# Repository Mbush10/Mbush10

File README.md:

- 👋 Hi, I’m @Mbush10
- 👀 I’m interested in ...
- 🌱 I’m currently learning ...
- 💞️ I’m looking to collaborate on ...
- 📫 How to reach me ...

<!---
Mbush10/Mbush10 is a ✨ special ✨ repository because its `README.md` (this file) appears on your GitHub profile.
You can click the Preview link to take a look at your changes.
--->

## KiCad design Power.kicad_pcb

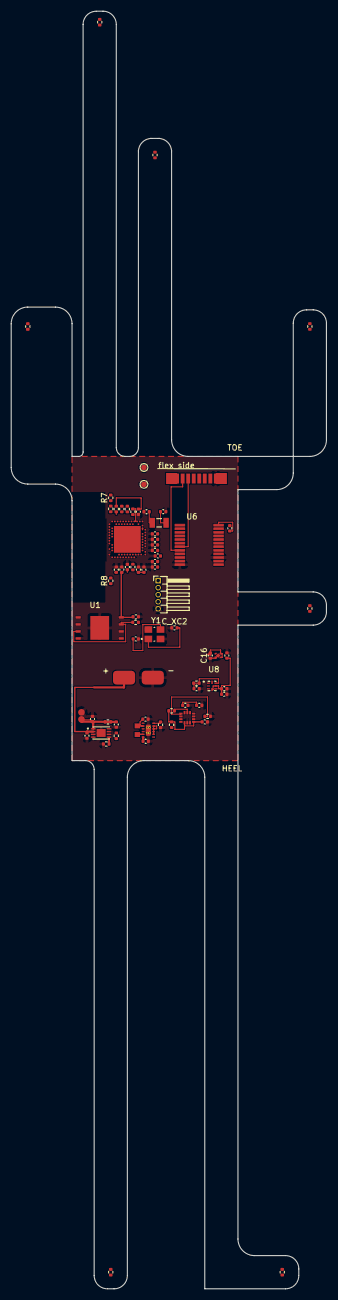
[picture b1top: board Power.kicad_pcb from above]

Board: 2 copper layers, 57.0 x 231.0 mm, 73 parts (0 on the bottom side), 53 nets.

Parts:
C1: 0.1uF; C_0402_1005Metric
C2, C3: 10µF; C_0402_1005Metric
C4, C12, C13, C14, C19, C20, C21: 100nF; C_0402_1005Metric
C5, C6, C7, C8, C9, C10, C11: C; C_0402_1005Metric
C15: 1 µF; C_0402_1005Metric
C16, C17: 1µF; C_0402_1005Metric
C18: 4.7nF; C_0402_1005Metric
C_IMU_IO1: 100nF; C_0402_1005Metric
C_IMU_VDD1: 1 µF; C_0402_1005Metric
C_IMU_VDD2: 100nF; C_0402_1005Metric
C_MCP_IN1: 1uF; C_0402_1005Metric
C_MCP_OUT1: 4.7µF; C_0402_1005Metric
C_RF1_1, C_RF2_1: DNP; C_0402_1005Metric
C_XC1, C_XC2: 18pF; C_0402_1005Metric
C_XL1, C_XL2: 22pF; C_0402_1005Metric
J1: POGO_CHG_2PAD_1P27
J_BAT1: BAT; BAT_SOLDER_2PAD_2P5x4P0_G1P2
J_FSR1: FSR_ARRAY; FSR_FLEX_1x08_P1.0
J_FSR_GND1, J_FSR_GND2: FSR_GND; TestPoint_Pad_D1.0mm
J_SWD1: Conn_01x05; PinHeader_1x05_P1.27mm_Horizontal
L1: KLZ1608MHR4R7WTD25; INDC1608X95N
R1, R3, R9: 10k; R_0402_1005Metric
R2: 100k; R_0402_1005Metric
R4, R5, R6, R7: 330Ω; R_0402_1005Metric
R8: 1kΩ; R_0402_1005Metric
R10: 0; R_0402_1005Metric
R11: 1k; R_0402_1005Metric
R_CTRL1: 1kΩ; R_0402_1005Metric
R_MCP_PROG1: 2k; R_0402_1005Metric
R_PULL1, R_PULL2, R_PULL3, R_PULL4, R_PULL5, R_PULL6, R_PULL7: 47k; R_0402_1005Metric
R_RF1_1: 0R; R_0402_1005Metric
R_SA0: 10k; R_0402_1005Metric
R_SCL1: 4.7k; R_0402_1005Metric
R_SDA1: 4.7k; R_0402_1005Metric
TPS6274x1: TEXAS instrument at 11
U1: W25Q64JVZEIM; SON127P600X800X80-9N
U2: NRF52840-QIAA-R7; NORDIC_NRF52840-QIAA-R7
U3: MCP73831-2ACI_MC; SON50P200X300X100-9N
U4: TPS7A0233PDQNR; IC_TPS7A0233PDQNR
U6: CD74HC4067SM96; SOP65P780X200-24N
U7: LSM6DSOX; PQFN50P250X300X86-14N
U8: ADS7042IRUGR; QFN50P150X150X40-8N
Y1: C3E-32.000-12-1530-X-R; XTAL_C3E-32.000-12-1530-X-R
Y2: CTS3-32.768-12.5-20-R; XTAL_CTS3-32.768-12.5-20-R

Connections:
/3V3_AON: C17.1, C19.1, C20.1, C21.1, C_IMU_IO1.1, C_IMU_VDD1.1, C_IMU_VDD2.1, R9.1, R_PULL1.1, R_PULL2.1, R_PULL3.1, R_PULL4.1, R_PULL5.1, R_PULL6.1, R_PULL7.1, R_SCL1.1, R_SDA1.1, U4.1 (OUT), U6.24 (VCC), U7.5 (VDDIO), U7.8 (VDD), U7.12 (CS), U8.4 (DVDD), U8.6 (AVDD)
/ADC_CS: U2.AC15 (P0.19), U8.1 (~CS)
/CHG_IN_5V: C14.2, C_MCP_IN1.2, J1.1 (VBUS), R10.1, R10.2, U3.1 (VDD)
/CHG_STAT: R8.2, R9.2, U3.3 (STAT)
/FLASH_CS: R7.1, U1.1 (~CS)
/MUX_A0: U2.AD16 (P0.20), U6.10 (S0)
/MUX_A1: U2.AC17 (P0.21), U6.11 (S1)
/MUX_A2: U2.AD18 (P0.22), U6.14 (S2)
/MUX_A3: U2.AC19 (P0.23), U6.13 (S3)
/P0.24: R_SCL1.2, U2.AD20 (P0.24), U7.13 (SCL)
/P0.25: R_SDA1.2, U2.AC21 (P0.25), U7.14 (SDA)
/P0.26: U2.G1 (P0.26), U7.4 (INT1)
/PCB_ANT: C_RF1_1.1, C_RF2_1.1, R_RF1_1.2
/R1: R2.2, R_CTRL1.1, TPS6274x1.4 (CTRL), TPS6274x1.12 (EN)
/SPI_MISO: R6.1, U1.2 (DO(IO1)), U8.2 (SDO)
/SPI_MOSI: R5.1, U1.5 (DI(IO0))
/SPI_SCK: R4.1, U1.6 (CLK), U8.3 (SCLK)
/SWDCLK: J_SWD1.3, U2.AA24 (SWDCLK)
/SWDIO: J_SWD1.2, U2.AC24 (SWDIO)
/Sensors_AnalogScan/ADC_IN: C18.1, R11.1, R11.2, U6.1 (COMMON_I/O), U8.7 (AINP)
/Sensors_AnalogScan/FSR1: J_FSR1.1, R_PULL1.2, U6.9 (I0)
/Sensors_AnalogScan/FSR2: J_FSR1.2, R_PULL2.2, U6.8 (I1)
/Sensors_AnalogScan/FSR3: J_FSR1.3, R_PULL3.2, U6.7 (I2)
/Sensors_AnalogScan/FSR4: J_FSR1.4, R_PULL4.2, U6.6 (I3)
/Sensors_AnalogScan/FSR5: J_FSR1.5, R_PULL5.2, U6.5 (I4)
/Sensors_AnalogScan/FSR6: J_FSR1.6, R_PULL6.2, U6.4 (I5)
/Sensors_AnalogScan/FSR7: J_FSR1.7, R_PULL7.2, U6.3 (I6)
/VBAT_RAW: C2.1, C16.2, C_MCP_OUT1.1, J_BAT1.1, TPS6274x1.1 (VIN), TPS6274x1.8 (VSEL4), TPS6274x1.9 (VSEL3), TPS6274x1.10 (VSEL2), TPS6274x1.11 (VSEL1), U3.2 (VBAT), U4.3 (EN), U4.4 (IN)
/XL1: C_XL1.2, U2.D2 (P0.00/XL1), Y2.1
/XL2: C_XL2.1, U2.F2 (P0.01/XL2), Y2.2
/nRESET: C4.2, J_SWD1.4, R3.2, U2.AC13 (P0.18/~RESET)
GND: C1.2, C2.2, C3.1, C4.1, C5.1, C6.1, C7.1, C8.1, C9.1, C10.1, C11.1, C12.2, C13.2, C14.1, C15.2, C16.1, C17.2, C18.2, C19.2, C20.2, C21.2, C_IMU_IO1.2, C_IMU_VDD1.2, C_IMU_VDD2.2, C_MCP_IN1.1, C_MCP_OUT1.2, C_RF1_1.2, C_RF2_1.2, C_XC1.2, C_XC2.1, C_XL1.1, C_XL2.2, J1.2 (GND), J_BAT1.2, J_FSR1.8, J_FSR_GND1.1, J_FSR_GND2.1, J_SWD1.5, R2.1, R_MCP_PROG1.2, R_SA0.2, TPS6274x1.3 (GND), TPS6274x1.13 (PAD), U1.4 (GND), U1.9 (EXP), U2.B7 (VSS), U2.EXP, U2.F23 (VSS_PA), U3.4 (VSS), U3.9 (EP), U4.2 (GND), U4.5 (THERMAL_PAD), U6.12 (GND), U6.15 (~E), U7.6 (GND), U7.7 (GND), U8.5 (GND), U8.8 (AINM), Y1.2 (GND), Y1.4 (GND)
unnamed: L1.1, TPS6274x1.2 (SW)
unnamed: R1.1, U1.3 (~WP(IO2)), U1.7 (~HOLD/RESET(IO3))
unnamed: R_RF1_1.1, U2.H23 (ANT)
unnamed: R_CTRL1.2, U2.AD8 (P0.13)
unnamed: R4.2, U2.AC9 (P0.14)
unnamed: R5.2, U2.AD10 (P0.15)
unnamed: R6.2, U2.AC11 (P0.16)
unnamed: R7.2, U2.AD12 (P0.17)
unnamed: R8.1, U2.U24 (P1.04)
unnamed: C5.2, U2.C1 (DEC1)
unnamed: C9.2, U2.A18 (DEC2)
unnamed: C6.2, U2.D23 (DEC3)
unnamed: C7.2, U2.B5 (DEC4)
unnamed: C10.2, U2.N24 (DEC5)
unnamed: C11.2, U2.E24 (DEC6)
unnamed: C8.2, U2.AC5 (DECUSB)
unnamed: C_XC1.1, U2.B24 (XC1), Y1.3
unnamed: C_XC2.2, U2.A23 (XC2), Y1.1
unnamed: R_MCP_PROG1.1, U3.5 (PROG)
unnamed: R_SA0.1, U7.1 (SDO/SA0)
VDD: C1.1, C3.2, C12.1, C13.1, C15.1, J_SWD1.1, L1.2, R1.2, R3.1, TPS6274x1.5 (VOUT), U1.8 (VCC), U2.A22 (VDD), U2.AD14 (VDD), U2.AD23 (VDD), U2.B1 (VDD), U2.W1 (VDD), U2.Y2 (VDDH)

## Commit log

2026-01-24 Add Fantasy Software Engineer League framework
    Create the foundational structure for a fantasy sports-style league
    for software engineers:
    - League structure documentation with format, rules, and flow
    - Core data models (League, Team, Engineer, Matchup, Score, Trade)
    - League management system for roster, draft, and matchup operations
    - Configurable scoring engine with metric presets (GitHub, Agile, Quality)
